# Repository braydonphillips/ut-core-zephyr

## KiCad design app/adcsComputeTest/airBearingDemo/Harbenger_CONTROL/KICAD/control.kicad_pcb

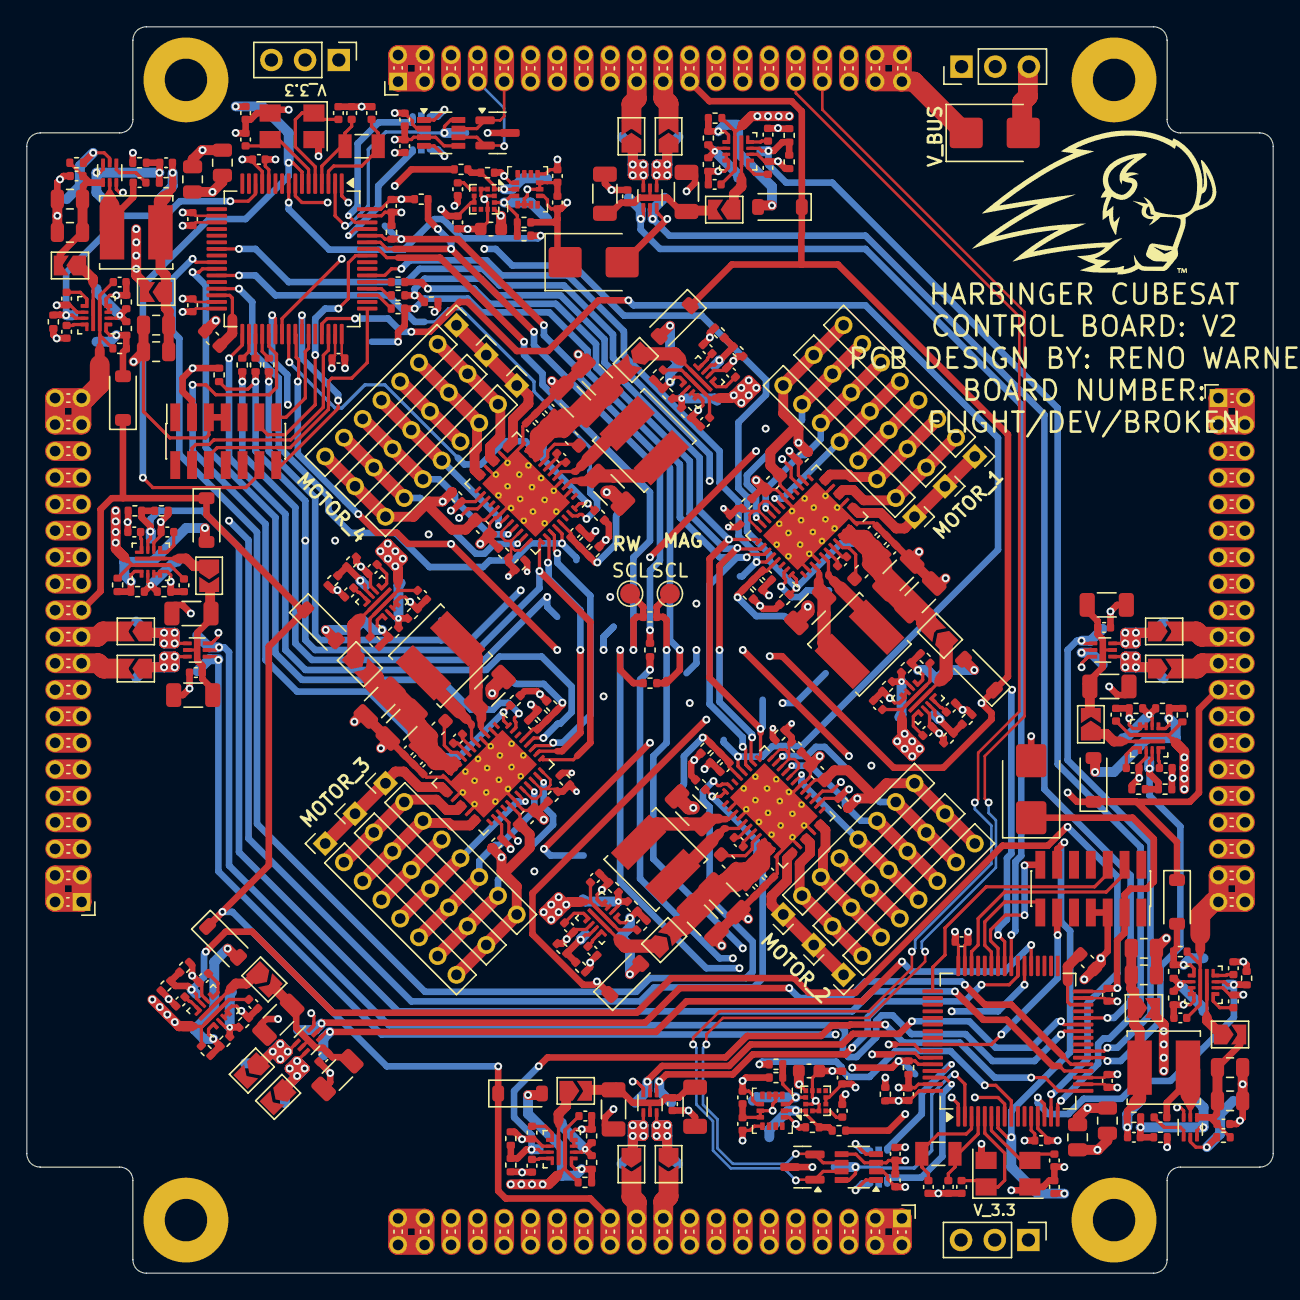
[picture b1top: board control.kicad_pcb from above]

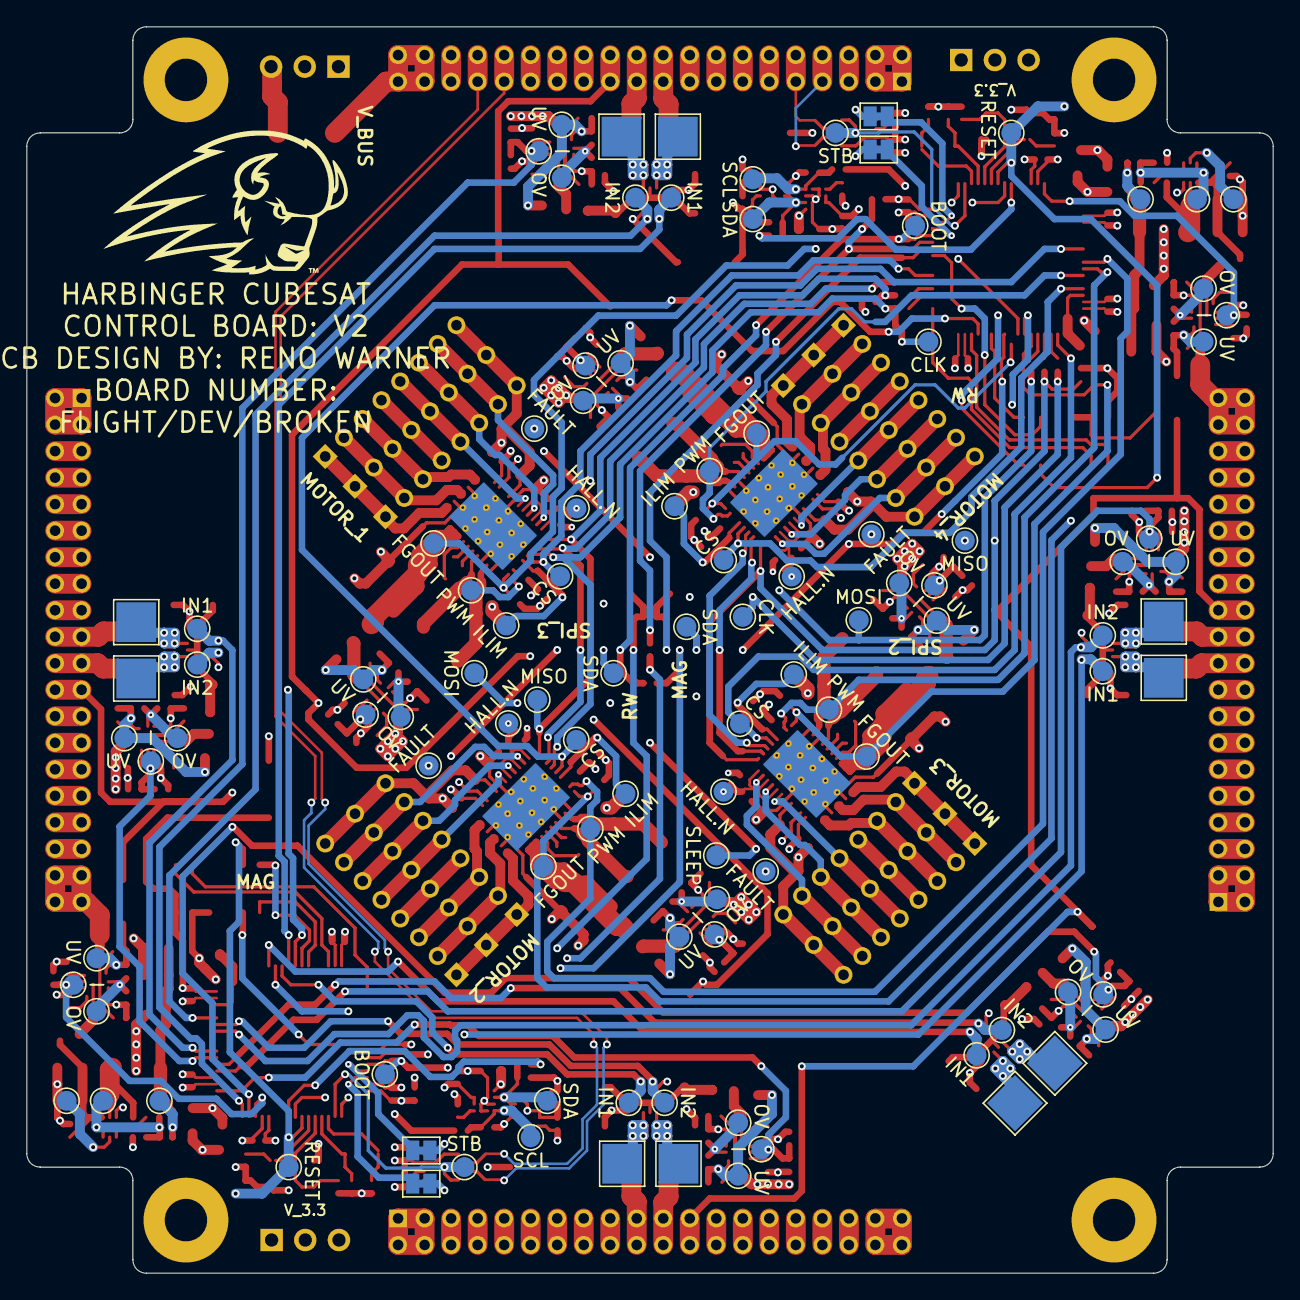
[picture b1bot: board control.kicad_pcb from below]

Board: 4 copper layers, 94.0 x 94.0 mm, 460 parts (106 on the bottom side), 301 nets.

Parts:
C1, C4, C5, C6, C8, C9, C10, C11, C12, C19, C22, C25, C27, C28, C31, C34, C37, C38, C39, C40, C41, C42, C49, C52, C53, C54, C55, C62, C65, C68, C69, C70, C71, C78, C81, C84, C87, C90, C93, C96, C98, C103, C104, C106, C108, C109, C110, C116, C117, C118, C121, C123, C128, C129, C131, C133, C134, C135, C141, C142: 100nF; C_0402_1005Metric
C2, C3, C23, C24, C32, C33, C35, C36, C50, C51, C63, C64, C79, C80, C85, C86, C88, C89, C94, C95, C119, C120: 4.7nF; C_0402_1005Metric
C7, C16, C18, C26, C46, C48, C59, C61, C75, C77: 1uF; C_0603_1608Metric
C13, C14, C15, C20, C21, C29, C30, C43, C44, C45, C56, C57, C58, C66, C67, C72, C73, C74, C82, C83, C91, C92: 22uF; C_1206_3216Metric
C17, C47, C60, C76: 47nF; C_0402_1005Metric
C97, C122: 47pF; C_0402_1005Metric
C99, C100, C101, C102, C105, C107, C124, C125, C126, C127, C130, C132: 10uF; C_0805_2012Metric
C111, C136: 4.7uF; C_0603_1608Metric
C112, C113, C137, C138: 6pF; C_0402_1005Metric
C114, C115, C139, C140: 12pF; C_0402_1005Metric
D1: SMBJ10A; D_SMB
D2, D6: SMLVT3V3; D_SMB
D3, D4, D5, D7, D8, D9, D10, D11, D12, D13, D14: BAT43W; D_SOD-123
D15, D16: ESD752DBZR; SOT-23
H1, H2, H3, H4: MountingHole_3.2mm_M3_Pad
J1, J2, J3, J4: TMM-120-01-F-D-RA; PinHeader_2x20_P2.00mm_Horizontal
J5, J6, J7, J8, J9, J10, J11, J12, J13, J14, J15, J16: CONN_1x08_2; PinHeader_1x08_P2.00mm_Vertical
J17, J18, J20: CONN_1x03_2.54; PinHeader_1x03_P2.54mm_Vertical
J19, J21: FTSH-107-01-L-DV-K; PinSocket_2x07_P1.27mm_Vertical_SMD
JP1, JP2, JP3, JP4, JP5, JP6, JP7, JP8, JP9, JP10, JP11, JP12, JP13, JP14, JP15, JP16, JP17, JP18, JP19, JP20, JP21, JP22, JP25: SolderJumper_2_Open; SolderJumper-2_P1.3mm_Open_TrianglePad1.0x1.5mm
JP23, JP24, JP26, JP27: Jumper_2_Bridged; SolderJumper-2_P1.3mm_Bridged_Pad1.0x1.5mm
L1, L2, L3, L4: LQH5BPN220MT0L; L_Murata_5x5
L5, L7: LQH5BPN2R2NT0L; L_Murata_5x5
R1, R5, R7, R8, R15, R16, R17, R18, R21, R22, R23, R24, R25, R28, R29, R31, R32, R33, R34, R36, R37, R38, R39, R40, R41, R42, R44, R45, R46, R47, R48, R49, R52, R53, R56, R57, R58, R59, R61, R62, R63, R64, R67, R68, R69, R70, R72, R73, R74, R75, R78, R79, R81, R82, R83, R84, R86, R87, R89, R90, R91, R92, R94, R95, R99, R101, R102, R106: 4.7kΩ; R_0402_1005Metric
R2, R3, R4, R9, R10, R11, R12, R13, R14, R19, R20, R50, R51: 100Ω; R_0402_1005Metric
R6, R30, R35, R43, R60, R71, R80, R85, R88, R93, R98, R100, R105: 30kΩ; R_0402_1005Metric
R26, R54, R65, R76: 220kΩ; R_0402_1005Metric
R27, R55, R66, R77, R96, R97, R103, R104: 133kΩ; R_0402_1005Metric
TP1, TP25, TP32, TP39, TP50, TP59, TP70, TP77, TP80, TP87, TP96: UV; TestPoint_Pad_D1.5mm
TP2, TP26, TP33, TP40, TP51, TP60, TP71, TP78, TP81, TP88, TP97: OV; TestPoint_Pad_D1.5mm
TP3, TP27, TP34, TP41, TP52, TP61, TP72, TP79, TP82, TP89, TP98: I; TestPoint_Pad_D1.5mm
TP4, TP7: MISO; TestPoint_Pad_D1.5mm
TP5, TP8: MOSI; TestPoint_Pad_D1.5mm
TP6, TP9: CLK; TestPoint_Pad_D1.5mm
TP10: SLEEP; TestPoint_Pad_D1.5mm
TP11, TP13, TP35, TP42: SCL; TestPoint_Pad_D1.5mm
TP12, TP14, TP36, TP43: SDA; TestPoint_Pad_D1.5mm
TP15, TP28, TP37, TP73, TP85: +; TestPoint_Pad_3.0x3.0mm
TP16, TP29, TP38, TP74, TP86: -; TestPoint_Pad_3.0x3.0mm
TP17, TP44, TP53, TP64: HALL.N; TestPoint_Pad_D1.5mm
TP18, TP45, TP54, TP65: ILIM; TestPoint_Pad_D1.5mm
TP19, TP46, TP55, TP66: FAULT; TestPoint_Pad_D1.5mm
TP20, TP47, TP56, TP67: FGOUT; TestPoint_Pad_D1.5mm
TP21, TP48, TP57, TP68: PWM; TestPoint_Pad_D1.5mm
TP22, TP49, TP58, TP69: CS; TestPoint_Pad_D1.5mm
TP23, TP30, TP62, TP75, TP83: IN1; TestPoint_Pad_D1.5mm
TP24, TP31, TP63, TP76, TP84: IN2; TestPoint_Pad_D1.5mm
TP90, TP99: EN; TestPoint_Pad_D1.5mm
TP91, TP100: V; TestPoint_Pad_D1.5mm
TP92, TP101: FB; TestPoint_Pad_D1.5mm
TP93, TP102: RESET; TestPoint_Pad_D1.5mm
TP94, TP103: BOOT; TestPoint_Pad_D1.5mm
TP95, TP104: STB; TestPoint_Pad_D1.5mm
U1, U6, U9, U10, U13, U15, U18, U20, U21, U23, U27: TPS259474L; Texas_RPW0010A
U2, U11: LSM6DSO; STM_LGA-14L
U3, U7: LIS3MDL; LGA-12_2x2mm_P0.5mm
U4, U12, U14, U17: MCT8316ZR; Texas_RGF40
U5, U8, U16, U19, U22: DRV8212DRL; Texas_DRL0006A
U24, U28: TPS562243; Texas_DRL0006A
U25, U29: STM32U5A5RJTx; LQFP-64_10x10mm_P0.5mm
U26, U30: TCAN3413DDFR; SOT-23-THIN
Y1, Y3: ECS-80-12-30BQ-JES-TR; Crystal_SMD_5032-4Pin_5.0x3.2mm
Y2, Y4: ECS-.327-6-34QCS-TR; Crystal_SMD_3215-2Pin_3.2x1.5mm

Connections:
/A.SCL: R3.2, TP13.1, U25.58 (PB6)
/A.SDA: R1.2, R2.2, TP14.1, U25.59 (PB7)
/B.SCL: R3.1, R5.2, TP35.1, U29.58 (PB6)
/B.SDA: R2.1, TP36.1, U29.59 (PB7)
/CAN_A.H: D15.1 (K), J2.9, J2.10, U26.7 (CAN_H)
/CAN_A.L: D15.2 (K), J2.7, J2.8, U26.6 (CAN_L)
/CAN_B.H: D16.1 (K), J2.31, J2.32, U30.7 (CAN_H)
/CAN_B.L: D16.2 (K), J2.33, J2.34, U30.6 (CAN_L)
/CONNECTOR_X+/GPIO: J2.29, J2.30
/CONNECTOR_X+/I2C.SCL: J2.15, J2.16
/CONNECTOR_X+/I2C.SDA: J2.13, J2.14
/CONNECTOR_X+/RESERVED: J2.17, J2.18
/CONNECTOR_X+/USB.DM: J2.27, J2.28
/CONNECTOR_X+/USB.DP: J2.25, J2.26
/CONNECTOR_X+/V_3.3: J2.11, J2.12
/CONNECTOR_X+/V_SOLAR: J2.1, J2.2, J2.3, J2.4
/CONNECTOR_X-/CAN_A.H: J1.9, J1.10
/CONNECTOR_X-/CAN_A.L: J1.7, J1.8
/CONNECTOR_X-/CAN_B.H: J1.31, J1.32
/CONNECTOR_X-/CAN_B.L: J1.33, J1.34
/CONNECTOR_X-/GPIO: J1.29, J1.30
/CONNECTOR_X-/I2C.SCL: J1.15, J1.16
/CONNECTOR_X-/I2C.SDA: J1.13, J1.14
/CONNECTOR_X-/RESERVED: J1.17, J1.18
/CONNECTOR_X-/USB.DM: J1.27, J1.28
/CONNECTOR_X-/USB.DP: J1.25, J1.26
/CONNECTOR_X-/V_3.3: J1.11, J1.12
/CONNECTOR_X-/V_SOLAR: J1.1, J1.2, J1.3, J1.4
/CONNECTOR_Y+/CAN_A.H: J3.9, J3.10
/CONNECTOR_Y+/CAN_A.L: J3.7, J3.8
/CONNECTOR_Y+/CAN_B.H: J3.31, J3.32
/CONNECTOR_Y+/CAN_B.L: J3.33, J3.34
/CONNECTOR_Y+/GPIO: J3.29, J3.30
/CONNECTOR_Y+/I2C.SCL: J3.15, J3.16
/CONNECTOR_Y+/I2C.SDA: J3.13, J3.14
/CONNECTOR_Y+/RESERVED: J3.17, J3.18
/CONNECTOR_Y+/USB.DM: J3.27, J3.28
/CONNECTOR_Y+/USB.DP: J3.25, J3.26
/CONNECTOR_Y+/V_3.3: J3.11, J3.12
/CONNECTOR_Y+/V_SOLAR: J3.1, J3.2, J3.3, J3.4
/CONNECTOR_Y-/CAN_A.H: J4.9, J4.10
/CONNECTOR_Y-/CAN_A.L: J4.7, J4.8
/CONNECTOR_Y-/CAN_B.H: J4.31, J4.32
/CONNECTOR_Y-/CAN_B.L: J4.33, J4.34
/CONNECTOR_Y-/GPIO: J4.29, J4.30
/CONNECTOR_Y-/I2C.SCL: J4.15, J4.16
/CONNECTOR_Y-/I2C.SDA: J4.13, J4.14
/CONNECTOR_Y-/RESERVED: J4.17, J4.18
/CONNECTOR_Y-/USB.DM: J4.27, J4.28
/CONNECTOR_Y-/USB.DP: J4.25, J4.26
/CONNECTOR_Y-/V_3.3: J4.11, J4.12
/CONNECTOR_Y-/V_SOLAR: J4.1, J4.2, J4.3, J4.4
/MAGNETORQUERS/COMMAND/EFUSE_LATCHED/DVDT: C120.1, U27.7 (DVDT)
/MAGNETORQUERS/COMMAND/EFUSE_LATCHED/ITIMER: C119.1, U27.10 (ITIMER)
/MAGNETORQUERS/COMMAND/EFUSE_LATCHED/OVLO: R101.2, R102.1, TP97.1, U27.2 (OVLO)
/MAGNETORQUERS/COMMAND/EFUSE_LATCHED/UVLO: D7.2 (A), R100.2, R101.1, TP96.1, U27.1 (EN/UVLO)
/MAGNETORQUERS/COMMAND/EFUSE_LATCHED/V_OUT: JP8.1 (A), U27.6 (OUT)
/MAGNETORQUERS/COMMAND/MCU/VCAP: C136.1, U29.30 (VCAP)
/MAGNETORQUERS/COMMAND/SMPS(3.3V)/SMPS/FB: C122.1, R103.2, R105.1, TP101.1, U28.6 (FB)
/MAGNETORQUERS/COMMAND/SMPS(3.3V)/SMPS/SW: C121.2, L7.1, U28.2 (SW)
/MAGNETORQUERS/COMMAND/SMPS(3.3V)/SMPS/V_OUT: C122.2, C126.1, C127.1, JP25.1 (A), L7.2, R103.1, TP100.1
/MAGNETORQUERS/COMMAND/SMPS(3.3V)/V_IN: C123.1, C124.1, C125.1, JP8.2 (B), R104.1, U28.1 (VIN)
/MAGNETORQUERS/COMMAND/SWD.NRST: C129.1, J21.12, TP102.1, U29.7 (NRST)
/MAGNETORQUERS/I2C_3.SCL: R48.1, R50.2, TP42.1, U2.13 (SCL/SPC), U3.1 (SCL/SPL)
/MAGNETORQUERS/I2C_3.SDA: R49.1, R51.2, TP43.1, U2.14 (SDA/SDI/SDO), U3.11 (SDA/SDI/SDO)
/MAGNETORQUERS/MAGNETORQUER_X+/BRUSHED_DRIVER/OUT_1: JP20.1 (A), TP85.1, U22.6 (OUT1)
/MAGNETORQUERS/MAGNETORQUER_X+/BRUSHED_DRIVER/OUT_2: JP21.1 (A), TP86.1, U22.4 (OUT2)
/MAGNETORQUERS/MAGNETORQUER_X+/BRUSHED_DRIVER/V_IN: C90.1, C91.1, C92.1, JP19.2 (B), U22.5 (VM)
/MAGNETORQUERS/MAGNETORQUER_X+/EFUSE_LATCHED/DVDT: C89.1, U21.7 (DVDT)
/MAGNETORQUERS/MAGNETORQUER_X+/EFUSE_LATCHED/ITIMER: C88.1, U21.10 (ITIMER)
/MAGNETORQUERS/MAGNETORQUER_X+/EFUSE_LATCHED/OVLO: R89.2, R90.1, TP81.1, U21.2 (OVLO)
/MAGNETORQUERS/MAGNETORQUER_X+/EFUSE_LATCHED/UVLO: D14.2 (A), R88.2, R89.1, TP80.1, U21.1 (EN/UVLO)
/MAGNETORQUERS/MAGNETORQUER_X+/EFUSE_LATCHED/V_OUT: JP19.1 (A), U21.6 (OUT)
/MAGNETORQUERS/MAGNETORQUER_X-/BRUSHED_DRIVER/OUT_1: JP3.1 (A), TP15.1, U5.6 (OUT1)
/MAGNETORQUERS/MAGNETORQUER_X-/BRUSHED_DRIVER/OUT_2: JP4.1 (A), TP16.1, U5.4 (OUT2)
/MAGNETORQUERS/MAGNETORQUER_X-/BRUSHED_DRIVER/V_IN: C19.1, C20.1, C21.1, JP2.2 (B), U5.5 (VM)
/MAGNETORQUERS/MAGNETORQUER_X-/EFUSE_LATCHED/DVDT: C24.1, U6.7 (DVDT)
/MAGNETORQUERS/MAGNETORQUER_X-/EFUSE_LATCHED/ITIMER: C23.1, U6.10 (ITIMER)
/MAGNETORQUERS/MAGNETORQUER_X-/EFUSE_LATCHED/OVLO: R31.2, R32.1, TP26.1, U6.2 (OVLO)
/MAGNETORQUERS/MAGNETORQUER_X-/EFUSE_LATCHED/UVLO: D4.2 (A), R30.2, R31.1, TP25.1, U6.1 (EN/UVLO)
/MAGNETORQUERS/MAGNETORQUER_X-/EFUSE_LATCHED/V_OUT: JP2.1 (A), U6.6 (OUT)
/MAGNETORQUERS/MAGNETORQUER_Y+/BRUSHED_DRIVER/OUT_1: JP6.1 (A), TP28.1, U8.6 (OUT1)
/MAGNETORQUERS/MAGNETORQUER_Y+/BRUSHED_DRIVER/OUT_2: JP7.1 (A), TP29.1, U8.4 (OUT2)
/MAGNETORQUERS/MAGNETORQUER_Y+/BRUSHED_DRIVER/V_IN: C28.1, C29.1, C30.1, JP5.2 (B), U8.5 (VM)
/MAGNETORQUERS/MAGNETORQUER_Y+/EFUSE_LATCHED/DVDT: C33.1, U9.7 (DVDT)
/MAGNETORQUERS/MAGNETORQUER_Y+/EFUSE_LATCHED/ITIMER: C32.1, U9.10 (ITIMER)
/MAGNETORQUERS/MAGNETORQUER_Y+/EFUSE_LATCHED/OVLO: R36.2, R37.1, TP33.1, U9.2 (OVLO)
/MAGNETORQUERS/MAGNETORQUER_Y+/EFUSE_LATCHED/UVLO: D5.2 (A), R35.2, R36.1, TP32.1, U9.1 (EN/UVLO)
/MAGNETORQUERS/MAGNETORQUER_Y+/EFUSE_LATCHED/V_OUT: JP5.1 (A), U9.6 (OUT)
/MAGNETORQUERS/MAGNETORQUER_Y-/BRUSHED_DRIVER/OUT_1: JP10.1 (A), TP37.1, U16.6 (OUT1)
/MAGNETORQUERS/MAGNETORQUER_Y-/BRUSHED_DRIVER/OUT_2: JP11.1 (A), TP38.1, U16.4 (OUT2)
/MAGNETORQUERS/MAGNETORQUER_Y-/BRUSHED_DRIVER/V_IN: C65.1, C66.1, C67.1, JP9.2 (B), U16.5 (VM)
/MAGNETORQUERS/MAGNETORQUER_Y-/EFUSE_LATCHED/DVDT: C80.1, U18.7 (DVDT)
/MAGNETORQUERS/MAGNETORQUER_Y-/EFUSE_LATCHED/ITIMER: C79.1, U18.10 (ITIMER)
/MAGNETORQUERS/MAGNETORQUER_Y-/EFUSE_LATCHED/OVLO: R81.2, R82.1, TP71.1, U18.2 (OVLO)
/MAGNETORQUERS/MAGNETORQUER_Y-/EFUSE_LATCHED/UVLO: D8.2 (A), R80.2, R81.1, TP70.1, U18.1 (EN/UVLO)
/MAGNETORQUERS/MAGNETORQUER_Y-/EFUSE_LATCHED/V_OUT: JP9.1 (A), U18.6 (OUT)
/MAGNETORQUERS/MAGNETORQUER_Z/BRUSHED_DRIVER/OUT_1: JP17.1 (A), TP73.1, U19.6 (OUT1)
/MAGNETORQUERS/MAGNETORQUER_Z/BRUSHED_DRIVER/OUT_2: JP18.1 (A), TP74.1, U19.4 (OUT2)
/MAGNETORQUERS/MAGNETORQUER_Z/BRUSHED_DRIVER/V_IN: C81.1, C82.1, C83.1, JP16.2 (B), U19.5 (VM)
/MAGNETORQUERS/MAGNETORQUER_Z/EFUSE_LATCHED/DVDT: C86.1, U20.7 (DVDT)
/MAGNETORQUERS/MAGNETORQUER_Z/EFUSE_LATCHED/ITIMER: C85.1, U20.10 (ITIMER)
/MAGNETORQUERS/MAGNETORQUER_Z/EFUSE_LATCHED/OVLO: R86.2, R87.1, TP78.1, U20.2 (OVLO)
/MAGNETORQUERS/MAGNETORQUER_Z/EFUSE_LATCHED/UVLO: D13.2 (A), R85.2, R86.1, TP77.1, U20.1 (EN/UVLO)
/MAGNETORQUERS/MAGNETORQUER_Z/EFUSE_LATCHED/V_OUT: JP16.1 (A), U20.6 (OUT)
/MAGNETORQUERS/PA0: R38.2, TP98.1, U27.9 (ILM), U29.14 (PA0)
/MAGNETORQUERS/PA1: R83.2, R84.2, TP79.1, U20.9 (ILM), U29.15 (PA1)
/MAGNETORQUERS/PA2: R91.2, R92.2, TP82.1, U21.9 (ILM), U29.16 (PA2)
/MAGNETORQUERS/PA3: R22.2, R23.2, TP27.1, U6.9 (ILM), U29.17 (PA3)
/MAGNETORQUERS/PA4: R33.2, R34.2, TP34.1, U9.9 (ILM), U29.20 (PA4)
/MAGNETORQUERS/PA5: TP76.1, U19.2 (IN2), U29.21 (PA5)
/MAGNETORQUERS/PA6: R39.2, R40.2, TP72.1, U18.9 (ILM), U29.22 (PA6)
/MAGNETORQUERS/PA7: TP62.1, U16.1 (IN1), U29.23 (PA7)
/MAGNETORQUERS/PA8: TP63.1, U16.2 (IN2), U29.41 (PA8)
/MAGNETORQUERS/PA9: J21.14, U29.42 (PA9)
/MAGNETORQUERS/PA10: J21.13, U29.43 (PA10)
/MAGNETORQUERS/PA13: J21.4, U29.46 (PA13)
/MAGNETORQUERS/PA14: J21.6, U29.49 (PA14)
/MAGNETORQUERS/PB0: TP31.1, U8.2 (IN2), U29.26 (PB0)
/MAGNETORQUERS/PB1: TP24.1, U5.2 (IN2), U29.27 (PB1)
/MAGNETORQUERS/PB2: TP84.1, U22.2 (IN2), U29.28 (PB2)
/MAGNETORQUERS/PB5: J21.11, U29.57 (PB5)
/MAGNETORQUERS/PB8: JP27.1 (A), U29.61 (PB8)
/MAGNETORQUERS/PB9: JP26.1 (A), U29.62 (PB9)
/MAGNETORQUERS/PC0: R50.1, U29.8 (PC0)
/MAGNETORQUERS/PC1: R51.1, U29.9 (PC1)
/MAGNETORQUERS/PC6: TP75.1, U19.1 (IN1), U29.37 (PC6)
/MAGNETORQUERS/PC7: TP30.1, U8.1 (IN1), U29.38 (PC7)
/MAGNETORQUERS/PC8: TP23.1, U5.1 (IN1), U29.39 (PC8)
/MAGNETORQUERS/PC9: TP83.1, U22.1 (IN1), U29.40 (PC9)
/MAGNETORQUERS/PC13: TP104.1, U29.2 (PC13), U30.8 (STB)
/MAGNETORQUERS/PC14: C138.1, U29.3 (PC14), Y4.2
/MAGNETORQUERS/PC15: C137.1, U29.4 (PC15), Y4.1
/MAGNETORQUERS/PH0: C139.1, U29.5 (PH0), Y3.1
/MAGNETORQUERS/PH1: C140.2, U29.6 (PH1), Y3.3
/MAGNETORQUERS/PH3: R4.1, R106.1, TP103.1, U29.60 (PH3)
/MAGNETORQUERS/V_3.3: C4.1, C5.1, C6.1, C7.1, C128.1, C130.1, C131.1, C132.1, C133.1, C134.1, C135.1, C141.1, C142.1, D6.1 (K), J20.2, J21.3, JP25.2 (B), R5.1, R48.2, R49.2, U2.5 (VDD_IO), U2.8 (VDD), U2.12 (CS), U3.5 (VDD), U3.6 (VDD_IO), U3.10 (CS), U29.1 (VBAT), U29.13 (VDDA), U29.19 (VDD), U29.32 (VDD), U29.48 (VDDUSB), U29.64 (VDD), U30.3 (VCC), U30.5 (V_IO)
/MAGNET_X+.+: J2.19, J2.20, JP20.2 (B)
/MAGNET_X+.-: J2.21, J2.22, JP21.2 (B)
/MAGNET_X-.+: J1.19, J1.20, JP3.2 (B)
/MAGNET_X-.-: J1.21, J1.22, JP4.2 (B)
/MAGNET_Y+.+: J3.19, J3.20, JP6.2 (B)
/MAGNET_Y+.-: J3.21, J3.22, JP7.2 (B)
/MAGNET_Y-.+: J4.19, J4.20, JP10.2 (B)
/MAGNET_Y-.-: J4.21, J4.22, JP11.2 (B)
/REACTION WHEELS/COMMAND/EFUSE_LATCHED/DVDT: C95.1, U23.7 (DVDT)
/REACTION WHEELS/COMMAND/EFUSE_LATCHED/ITIMER: C94.1, U23.10 (ITIMER)
/REACTION WHEELS/COMMAND/EFUSE_LATCHED/OVLO: R94.2, R95.1, TP88.1, U23.2 (OVLO)
/REACTION WHEELS/COMMAND/EFUSE_LATCHED/UVLO: D3.2 (A), R93.2, R94.1, TP87.1, U23.1 (EN/UVLO)
/REACTION WHEELS/COMMAND/EFUSE_LATCHED/V_OUT: JP1.1 (A), U23.6 (OUT)
/REACTION WHEELS/COMMAND/MCU/VCAP: C111.1, U25.30 (VCAP)
/REACTION WHEELS/COMMAND/SMPS(3.3V)/SMPS/FB: C97.1, R96.2, R98.1, TP92.1, U24.6 (FB)
/REACTION WHEELS/COMMAND/SMPS(3.3V)/SMPS/SW: C96.2, L5.1, U24.2 (SW)
/REACTION WHEELS/COMMAND/SMPS(3.3V)/SMPS/V_OUT: C97.2, C101.1, C102.1, JP22.1 (A), L5.2, R96.1, TP91.1
/REACTION WHEELS/COMMAND/SMPS(3.3V)/V_IN: C98.1, C99.1, C100.1, JP1.2 (B), R97.1, U24.1 (VIN)
/REACTION WHEELS/COMMAND/SWD.NRST: C104.1, J19.12, TP93.1, U25.7 (NRST)
/REACTION WHEELS/CONTROL_1.CS: TP22.1, U4.36 (nSCS), U25.54 (PD2)
/REACTION WHEELS/CONTROL_1.FAULT: R29.2, TP19.1, U4.22 (nFAULT)
/REACTION WHEELS/CONTROL_1.FGOUT: R28.2, TP20.1, U4.40 (FGOUT), U25.39 (PC8)
/REACTION WHEELS/CONTROL_1.PWM: TP21.1, U4.39 (PWM), U25.23 (PA7)
/REACTION WHEELS/CONTROL_2.CS: TP49.1, U12.36 (nSCS), U25.45 (PA12)
/REACTION WHEELS/CONTROL_2.FAULT: R57.2, TP46.1, U12.22 (nFAULT)
/REACTION WHEELS/CONTROL_2.FGOUT: R56.2, TP47.1, U12.40 (FGOUT), U25.38 (PC7)
/REACTION WHEELS/CONTROL_2.PWM: TP48.1, U12.39 (PWM), U25.25 (PC5)
/REACTION WHEELS/CONTROL_3.CS: TP58.1, U14.36 (nSCS), U25.33 (PB12)
/REACTION WHEELS/CONTROL_3.FAULT: R68.2, TP55.1, U14.22 (nFAULT)
/REACTION WHEELS/CONTROL_3.FGOUT: R67.2, TP56.1, U14.40 (FGOUT), U25.37 (PC6)
/REACTION WHEELS/CONTROL_3.PWM: TP57.1, U14.39 (PWM), U25.26 (PB0)
/REACTION WHEELS/CONTROL_3.SLEEP: TP10.1, U4.23 (nSLEEP), U12.23 (nSLEEP), U14.23 (nSLEEP), U17.23 (nSLEEP), U25.41 (PA8)
/REACTION WHEELS/CONTROL_4.CS: TP69.1, U17.36 (nSCS), U25.29 (PB10)
/REACTION WHEELS/CONTROL_4.FAULT: R79.2, TP66.1, U17.22 (nFAULT)
/REACTION WHEELS/CONTROL_4.FGOUT: R78.2, TP67.1, U17.40 (FGOUT), U25.40 (PC9)
/REACTION WHEELS/CONTROL_4.PWM: TP68.1, U17.39 (PWM), U25.27 (PB1)
/REACTION WHEELS/I2C_3.SCL: R17.1, R19.2, TP11.1, U7.1 (SCL/SPL), U11.13 (SCL/SPC)
/REACTION WHEELS/I2C_3.SDA: R18.1, R20.2, TP12.1, U7.11 (SDA/SDI/SDO), U11.14 (SDA/SDI/SDO)
/REACTION WHEELS/PA0: R21.2, TP89.1, U23.9 (ILM), U25.14 (PA0)
/REACTION WHEELS/PA9: J19.14, U25.42 (PA9)
/REACTION WHEELS/PA10: J19.13, U25.43 (PA10)
/REACTION WHEELS/PA13: J19.4, U25.46 (PA13)
/REACTION WHEELS/PA14: J19.6, U25.49 (PA14)
/REACTION WHEELS/PB5: J19.11, U25.57 (PB5)
/REACTION WHEELS/PB8: JP24.1 (A), U25.61 (PB8)
/REACTION WHEELS/PB9: JP23.1 (A), U25.62 (PB9)
/REACTION WHEELS/PB13: R11.1, U25.34 (PB13)
/REACTION WHEELS/PB14: R9.1, U25.35 (PB14)
/REACTION WHEELS/PB15: R10.1, U25.36 (PB15)
/REACTION WHEELS/PC0: R19.1, U25.8 (PC0)
/REACTION WHEELS/PC1: R20.1, U25.9 (PC1)
/REACTION WHEELS/PC10: R14.1, U25.51 (PC10)
/REACTION WHEELS/PC11: R12.1, U25.52 (PC11)
/REACTION WHEELS/PC12: R13.1, U25.53 (PC12)
/REACTION WHEELS/PC13: TP95.1, U25.2 (PC13), U26.8 (STB)
/REACTION WHEELS/PC14: C113.1, U25.3 (PC14), Y2.2
/REACTION WHEELS/PC15: C112.1, U25.4 (PC15), Y2.1
/REACTION WHEELS/PH0: C114.1, U25.5 (PH0), Y1.1
/REACTION WHEELS/PH1: C115.2, U25.6 (PH1), Y1.3
/REACTION WHEELS/PH3: R4.2, R99.1, TP94.1, U25.60 (PH3)
/REACTION WHEELS/REACTION_WHEEL_1/BLDC_MOTOR_DRIVER/HALL.A: J8.5, J9.5, J10.5, U4.27 (HPA)
/REACTION WHEELS/REACTION_WHEEL_1/BLDC_MOTOR_DRIVER/HALL.B: J8.7, J9.7, J10.7, U4.31 (HPC)
/REACTION WHEELS/REACTION_WHEEL_1/BLDC_MOTOR_DRIVER/HALL.C: J8.6, J9.6, J10.6, U4.29 (HPB)
/REACTION WHEELS/REACTION_WHEEL_1/BLDC_MOTOR_DRIVER/HALL.N: R24.2, R25.1, TP17.1, U4.28 (HNA), U4.30 (HNB), U4.32 (HNC)
/REACTION WHEELS/REACTION_WHEEL_1/BLDC_MOTOR_DRIVER/ILIM: C10.1, R26.2, R27.1, TP18.1, U4.37 (ILIM)
/REACTION WHEELS/REACTION_WHEEL_1/BLDC_MOTOR_DRIVER/MOTOR.A: J8.1, J9.1, J10.1, U4.13 (OUTA), U4.14 (OUTA)
/REACTION WHEELS/REACTION_WHEEL_1/BLDC_MOTOR_DRIVER/MOTOR.B: J8.2, J9.2, J10.2, U4.16 (OUTB), U4.17 (OUTB)
/REACTION WHEELS/REACTION_WHEEL_1/BLDC_MOTOR_DRIVER/MOTOR.C: J8.3, J9.3, J10.3, U4.19 (OUTC), U4.20 (OUTC)
/REACTION WHEELS/REACTION_WHEEL_1/BLDC_MOTOR_DRIVER/V_AVDD: C18.1, J8.8, J9.8, J10.8, R24.1, R26.1, R28.1, R29.1, U4.25 (AVDD)
/REACTION WHEELS/REACTION_WHEEL_1/BLDC_MOTOR_DRIVER/V_IN: C9.2, C11.2, C12.2, C13.1, C14.1, C16.1, JP13.2 (B), U4.9 (VM), U4.10 (VM), U4.11 (VM)
/REACTION WHEELS/REACTION_WHEEL_1/EFUSE_LATCHED/DVDT: C3.1, U1.7 (DVDT)
/REACTION WHEELS/REACTION_WHEEL_1/EFUSE_LATCHED/ITIMER: C2.1, U1.10 (ITIMER)
/REACTION WHEELS/REACTION_WHEEL_1/EFUSE_LATCHED/I_LIM: R46.2, R47.2, TP3.1, U1.9 (ILM)
/REACTION WHEELS/REACTION_WHEEL_1/EFUSE_LATCHED/OVLO: R7.2, R8.1, TP2.1, U1.2 (OVLO)
/REACTION WHEELS/REACTION_WHEEL_1/EFUSE_LATCHED/UVLO: D10.2 (A), R6.2, R7.1, TP1.1, U1.1 (EN/UVLO)
/REACTION WHEELS/REACTION_WHEEL_1/EFUSE_LATCHED/V_OUT: JP13.1 (A), U1.6 (OUT)
/REACTION WHEELS/REACTION_WHEEL_2/BLDC_MOTOR_DRIVER/HALL.A: J5.5, J6.5, J7.5, U12.27 (HPA)
/REACTION WHEELS/REACTION_WHEEL_2/BLDC_MOTOR_DRIVER/HALL.B: J5.7, J6.7, J7.7, U12.31 (HPC)
/REACTION WHEELS/REACTION_WHEEL_2/BLDC_MOTOR_DRIVER/HALL.C: J5.6, J6.6, J7.6, U12.29 (HPB)
/REACTION WHEELS/REACTION_WHEEL_2/BLDC_MOTOR_DRIVER/HALL.N: R52.2, R53.1, TP44.1, U12.28 (HNA), U12.30 (HNB), U12.32 (HNC)
/REACTION WHEELS/REACTION_WHEEL_2/BLDC_MOTOR_DRIVER/ILIM: C40.1, R54.2, R55.1, TP45.1, U12.37 (ILIM)
/REACTION WHEELS/REACTION_WHEEL_2/BLDC_MOTOR_DRIVER/MOTOR.A: J5.1, J6.1, J7.1, U12.13 (OUTA), U12.14 (OUTA)
/REACTION WHEELS/REACTION_WHEEL_2/BLDC_MOTOR_DRIVER/MOTOR.B: J5.2, J6.2, J7.2, U12.16 (OUTB), U12.17 (OUTB)
/REACTION WHEELS/REACTION_WHEEL_2/BLDC_MOTOR_DRIVER/MOTOR.C: J5.3, J6.3, J7.3, U12.19 (OUTC), U12.20 (OUTC)
/REACTION WHEELS/REACTION_WHEEL_2/BLDC_MOTOR_DRIVER/V_AVDD: C48.1, J5.8, J6.8, J7.8, R52.1, R54.1, R56.1, R57.1, U12.25 (AVDD)
/REACTION WHEELS/REACTION_WHEEL_2/BLDC_MOTOR_DRIVER/V_IN: C39.2, C41.2, C42.2, C43.1, C44.1, C46.1, JP12.2 (B), U12.9 (VM), U12.10 (VM), U12.11 (VM)
/REACTION WHEELS/REACTION_WHEEL_2/EFUSE_LATCHED/DVDT: C36.1, U10.7 (DVDT)
/REACTION WHEELS/REACTION_WHEEL_2/EFUSE_LATCHED/ITIMER: C35.1, U10.10 (ITIMER)
/REACTION WHEELS/REACTION_WHEEL_2/EFUSE_LATCHED/I_LIM: R41.2, R42.2, TP41.1, U10.9 (ILM)
/REACTION WHEELS/REACTION_WHEEL_2/EFUSE_LATCHED/OVLO: R44.2, R45.1, TP40.1, U10.2 (OVLO)
/REACTION WHEELS/REACTION_WHEEL_2/EFUSE_LATCHED/UVLO: D9.2 (A), R43.2, R44.1, TP39.1, U10.1 (EN/UVLO)
/REACTION WHEELS/REACTION_WHEEL_2/EFUSE_LATCHED/V_OUT: JP12.1 (A), U10.6 (OUT)
/REACTION WHEELS/REACTION_WHEEL_3/BLDC_MOTOR_DRIVER/HALL.A: J11.5, J12.5, J13.5, U14.27 (HPA)
/REACTION WHEELS/REACTION_WHEEL_3/BLDC_MOTOR_DRIVER/HALL.B: J11.7, J12.7, J13.7, U14.31 (HPC)
/REACTION WHEELS/REACTION_WHEEL_3/BLDC_MOTOR_DRIVER/HALL.C: J11.6, J12.6, J13.6, U14.29 (HPB)
/REACTION WHEELS/REACTION_WHEEL_3/BLDC_MOTOR_DRIVER/HALL.N: R63.2, R64.1, TP53.1, U14.28 (HNA), U14.30 (HNB), U14.32 (HNC)
/REACTION WHEELS/REACTION_WHEEL_3/BLDC_MOTOR_DRIVER/ILIM: C53.1, R65.2, R66.1, TP54.1, U14.37 (ILIM)
/REACTION WHEELS/REACTION_WHEEL_3/BLDC_MOTOR_DRIVER/MOTOR.A: J11.1, J12.1, J13.1, U14.13 (OUTA), U14.14 (OUTA)
/REACTION WHEELS/REACTION_WHEEL_3/BLDC_MOTOR_DRIVER/MOTOR.B: J11.2, J12.2, J13.2, U14.16 (OUTB), U14.17 (OUTB)
/REACTION WHEELS/REACTION_WHEEL_3/BLDC_MOTOR_DRIVER/MOTOR.C: J11.3, J12.3, J13.3, U14.19 (OUTC), U14.20 (OUTC)
/REACTION WHEELS/REACTION_WHEEL_3/BLDC_MOTOR_DRIVER/V_AVDD: C61.1, J11.8, J12.8, J13.8, R63.1, R65.1, R67.1, R68.1, U14.25 (AVDD)
/REACTION WHEELS/REACTION_WHEEL_3/BLDC_MOTOR_DRIVER/V_IN: C52.2, C54.2, C55.2, C56.1, C57.1, C59.1, JP14.2 (B), U14.9 (VM), U14.10 (VM), U14.11 (VM)
/REACTION WHEELS/REACTION_WHEEL_3/EFUSE_LATCHED/DVDT: C51.1, U13.7 (DVDT)
/REACTION WHEELS/REACTION_WHEEL_3/EFUSE_LATCHED/ITIMER: C50.1, U13.10 (ITIMER)
/REACTION WHEELS/REACTION_WHEEL_3/EFUSE_LATCHED/I_LIM: R58.2, R59.2, TP52.1, U13.9 (ILM)
/REACTION WHEELS/REACTION_WHEEL_3/EFUSE_LATCHED/OVLO: R61.2, R62.1, TP51.1, U13.2 (OVLO)
/REACTION WHEELS/REACTION_WHEEL_3/EFUSE_LATCHED/UVLO: D11.2 (A), R60.2, R61.1, TP50.1, U13.1 (EN/UVLO)
/REACTION WHEELS/REACTION_WHEEL_3/EFUSE_LATCHED/V_OUT: JP14.1 (A), U13.6 (OUT)
/REACTION WHEELS/REACTION_WHEEL_4/BLDC_MOTOR_DRIVER/HALL.A: J14.5, J15.5, J16.5, U17.27 (HPA)
/REACTION WHEELS/REACTION_WHEEL_4/BLDC_MOTOR_DRIVER/HALL.B: J14.7, J15.7, J16.7, U17.31 (HPC)
/REACTION WHEELS/REACTION_WHEEL_4/BLDC_MOTOR_DRIVER/HALL.C: J14.6, J15.6, J16.6, U17.29 (HPB)
/REACTION WHEELS/REACTION_WHEEL_4/BLDC_MOTOR_DRIVER/HALL.N: R74.2, R75.1, TP64.1, U17.28 (HNA), U17.30 (HNB), U17.32 (HNC)
/REACTION WHEELS/REACTION_WHEEL_4/BLDC_MOTOR_DRIVER/ILIM: C69.1, R76.2, R77.1, TP65.1, U17.37 (ILIM)
/REACTION WHEELS/REACTION_WHEEL_4/BLDC_MOTOR_DRIVER/MOTOR.A: J14.1, J15.1, J16.1, U17.13 (OUTA), U17.14 (OUTA)
/REACTION WHEELS/REACTION_WHEEL_4/BLDC_MOTOR_DRIVER/MOTOR.B: J14.2, J15.2, J16.2, U17.16 (OUTB), U17.17 (OUTB)
/REACTION WHEELS/REACTION_WHEEL_4/BLDC_MOTOR_DRIVER/MOTOR.C: J14.3, J15.3, J16.3, U17.19 (OUTC), U17.20 (OUTC)
/REACTION WHEELS/REACTION_WHEEL_4/BLDC_MOTOR_DRIVER/V_AVDD: C77.1, J14.8, J15.8, J16.8, R74.1, R76.1, R78.1, R79.1, U17.25 (AVDD)
/REACTION WHEELS/REACTION_WHEEL_4/BLDC_MOTOR_DRIVER/V_IN: C68.2, C70.2, C71.2, C72.1, C73.1, C75.1, JP15.2 (B), U17.9 (VM), U17.10 (VM), U17.11 (VM)
/REACTION WHEELS/REACTION_WHEEL_4/EFUSE_LATCHED/DVDT: C64.1, U15.7 (DVDT)
/REACTION WHEELS/REACTION_WHEEL_4/EFUSE_LATCHED/ITIMER: C63.1, U15.10 (ITIMER)
/REACTION WHEELS/REACTION_WHEEL_4/EFUSE_LATCHED/I_LIM: R69.2, R70.2, TP61.1, U15.9 (ILM)
/REACTION WHEELS/REACTION_WHEEL_4/EFUSE_LATCHED/OVLO: R72.2, R73.1, TP60.1, U15.2 (OVLO)
/REACTION WHEELS/REACTION_WHEEL_4/EFUSE_LATCHED/UVLO: D12.2 (A), R71.2, R72.1, TP59.1, U15.1 (EN/UVLO)
/REACTION WHEELS/REACTION_WHEEL_4/EFUSE_LATCHED/V_OUT: JP15.1 (A), U15.6 (OUT)
/REACTION WHEELS/SPI_2.CLK: R11.2, TP6.1, U14.35 (SCLK), U17.35 (SCLK)
/REACTION WHEELS/SPI_2.MISO: R9.2, R15.2, TP4.1, U14.33 (SDO), U17.33 (SDO)
/REACTION WHEELS/SPI_2.MOSI: R10.2, TP5.1, U14.34 (SDI), U17.34 (SDI)
/REACTION WHEELS/SPI_3.CLK: R14.2, TP9.1, U4.35 (SCLK), U12.35 (SCLK)
/REACTION WHEELS/SPI_3.MISO: R12.2, R16.2, TP7.1, U4.33 (SDO), U12.33 (SDO)
/REACTION WHEELS/SPI_3.MOSI: R13.2, TP8.1, U4.34 (SDI), U12.34 (SDI)
/REACTION WHEELS/V_3.3: C25.1, C26.1, C37.1, C38.1, C103.1, C105.1, C106.1, C107.1, C108.1, C109.1, C110.1, C116.1, C117.1, D2.1 (K), J18.2, J19.3, JP22.2 (B), R1.1, R15.1, R16.1, R17.2, R18.2, U7.5 (VDD), U7.6 (VDD_IO), U7.10 (CS), U11.5 (VDD_IO), U11.8 (VDD), U11.12 (CS), U25.1 (VBAT), U25.13 (VDDA), U25.19 (VDD), U25.32 (VDD), U25.48 (VDDUSB), U25.64 (VDD), U26.3 (VCC), U26.5 (V_IO)
/SHUTDOWN: D3.1 (K), D4.1 (K), D5.1 (K), D7.1 (K), D8.1 (K), D9.1 (K), D10.1 (K), D11.1 (K), D12.1 (K), D13.1 (K), D14.1 (K), J1.23, J1.24, J2.23, J2.24, J3.23, J3.24, J4.23, J4.24
/V_BUS: C1.1, C22.1, C31.1, C34.1, C49.1, C62.1, C78.1, C84.1, C87.1, C93.1, C118.1, D1.1 (K), J1.37, J1.38, J1.39, J1.40, J2.37, J2.38, J2.39, J2.40, J3.37, J3.38, J3.39, J3.40, J4.37, J4.38, J4.39, J4.40, J17.2, R6.1, R30.1, R35.1, R43.1, R60.1, R71.1, R80.1, R85.1, R88.1, R93.1, R100.1, U1.5 (IN), U6.5 (IN), U9.5 (IN), U10.5 (IN), U13.5 (IN), U15.5 (IN), U18.5 (IN), U20.5 (IN), U21.5 (IN), U23.5 (IN), U27.5 (IN)
/V_GND: C1.2, C2.2, C3.2, C4.2, C5.2, C6.2, C7.2, C8.2, C9.1, C10.2, C11.1, C12.1, C13.2, C14.2, C15.1, C18.2, C19.2, C20.2, C21.2, C22.2, C23.2, C24.2, C25.2, C26.2, C27.2, C28.2, C29.2, C30.2, C31.2, C32.2, C33.2, C34.2, C35.2, C36.2, C37.2, C38.2, C39.1, C40.2, C41.1, C42.1, C43.2, C44.2, C45.1, C48.2, C49.2, C50.2, C51.2, C52.1, C53.2, C54.1, C55.1, C56.2, C57.2, C58.1, C61.2, C62.2, C63.2, C64.2, C65.2, C66.2, C67.2, C68.1, C69.2, C70.1, C71.1, C72.2, C73.2, C74.1, C77.2, C78.2, C79.2, C80.2, C81.2, C82.2, C83.2, C84.2, C85.2, C86.2, C87.2, C88.2, C89.2, C90.2, C91.2, C92.2, C93.2, C94.2, C95.2, C98.2, C99.2, C100.2, C101.2, C102.2, C103.2, C104.2, C105.2, C106.2, C107.2, C108.2, C109.2, C110.2, C111.2, C112.2, C113.2, C114.2, C115.1, C116.2, C117.2, C118.2, C119.2, C120.2, C123.2, C124.2, C125.2, C126.2, C127.2, C128.2, C129.2, C130.2, C131.2, C132.2, C133.2, C134.2, C135.2, C136.2, C137.2, C138.2, C139.2, C140.1, C141.2, C142.2, D1.2 (A), D2.2 (A), D6.2 (A), D15.3 (A), D16.3 (A), H1.1, H2.1, H3.1, H4.1, J1.5, J1.6, J1.35, J1.36, J2.5, J2.6, J2.35, J2.36, J3.5, J3.6, J3.35, J3.36, J4.5, J4.6, J4.35, J4.36, J5.4, J6.4, J7.4, J8.4, J9.4, J10.4, J11.4, J12.4, J13.4, J14.4, J15.4, J16.4, J17.1, J17.3, J18.1, J18.3, J19.5, J19.7, J20.1, J20.3, J21.5, J21.7, R8.2, R21.1, R22.1, R23.1, R25.2, R27.2, R32.2, R33.1, R34.1, R37.2, R38.1, R39.1, R40.1, R41.1, R42.1, R45.2, R46.1, R47.1, R53.2, R55.2, R58.1, R59.1, R62.2, R64.2, R66.2, R69.1, R70.1, R73.2, R75.2, R77.2, R82.2, R83.1, R84.1, R87.2, R90.2, R91.1, R92.1, R95.2, R98.2, R99.2, R102.2, R105.2, R106.2, U1.3 (PG), U1.4 (PGTH), U1.8 (GND), U2.1 (SDO/SA0), U2.2 (SDX), U2.3 (SCX), U2.6 (GND), U2.7 (GND), U3.2 (RESERVED), U3.3 (GND), U3.9 (SDO/SA1), U3.12 (RESERVED), U4.2 (AGND), U4.4 (GND_BK), U4.12 (PGND), U4.15 (PGND), U4.18 (PGND), U4.26 (AGND), U4.41 (TPAD), U5.3 (GND), U6.3 (PG), U6.4 (PGTH), U6.8 (GND), U7.2 (RESERVED), U7.3 (GND), U7.9 (SDO/SA1), U7.12 (RESERVED), U8.3 (GND), U9.3 (PG), U9.4 (PGTH), U9.8 (GND), U10.3 (PG), U10.4 (PGTH), U10.8 (GND), U11.1 (SDO/SA0), U11.2 (SDX), U11.3 (SCX), U11.6 (GND), U11.7 (GND), U12.2 (AGND), U12.4 (GND_BK), U12.12 (PGND), U12.15 (PGND), U12.18 (PGND), U12.26 (AGND), U12.41 (TPAD), U13.3 (PG), U13.4 (PGTH), U13.8 (GND), U14.2 (AGND), U14.4 (GND_BK), U14.12 (PGND), U14.15 (PGND), U14.18 (PGND), U14.26 (AGND), U14.41 (TPAD), U15.3 (PG), U15.4 (PGTH), U15.8 (GND), U16.3 (GND), U17.2 (AGND), U17.4 (GND_BK), U17.12 (PGND), U17.15 (PGND), U17.18 (PGND), U17.26 (AGND), U17.41 (TPAD), U18.3 (PG), U18.4 (PGTH), U18.8 (GND), U19.3 (GND), U20.3 (PG), U20.4 (PGTH), U20.8 (GND), U21.3 (PG), U21.4 (PGTH), U21.8 (GND), U22.3 (GND), U23.3 (PG), U23.4 (PGTH), U23.8 (GND), U24.3 (GND), U25.12 (VSSA), U25.18 (VSS), U25.31 (VSS), U25.47 (VSS), U25.63 (VSS), U26.2 (GND), U27.3 (PG), U27.4 (PGTH), U27.8 (GND), U28.3 (GND), U29.12 (VSSA), U29.18 (VSS), U29.31 (VSS), U29.47 (VSS), U29.63 (VSS), U30.2 (GND), Y1.2, Y1.4, Y3.2, Y3.4
unnamed: JP23.2 (B), U26.1 (TXD)
unnamed: JP24.2 (B), U26.4 (RXD)
unnamed: JP26.2 (B), U30.1 (TXD)
unnamed: JP27.2 (B), U30.4 (RXD)
unnamed: C8.1, U3.4 (C1)
unnamed: C16.2, U4.8 (CP)
unnamed: C17.1, U4.7 (CPH)
unnamed: C17.2, U4.6 (CPL)
unnamed: C15.2, L1.1, U4.3 (FB_BK)
unnamed: L1.2, U4.5 (SW_BK)
unnamed: C27.1, U7.4 (C1)
unnamed: C46.2, U12.8 (CP)
unnamed: C47.1, U12.7 (CPH)
unnamed: C47.2, U12.6 (CPL)
unnamed: C45.2, L2.1, U12.3 (FB_BK)
unnamed: L2.2, U12.5 (SW_BK)
unnamed: C59.2, U14.8 (CP)
unnamed: C60.1, U14.7 (CPH)
unnamed: C60.2, U14.6 (CPL)
unnamed: C58.2, L3.1, U14.3 (FB_BK)
unnamed: L3.2, U14.5 (SW_BK)
unnamed: C75.2, U17.8 (CP)
unnamed: C76.1, U17.7 (CPH)
unnamed: C76.2, U17.6 (CPL)
unnamed: C74.2, L4.1, U17.3 (FB_BK)
unnamed: L4.2, U17.5 (SW_BK)
unnamed: C96.1, U24.4 (BST)
unnamed: R97.2, TP90.1, U24.5 (EN)
unnamed: C121.1, U28.4 (BST)
unnamed: R104.2, TP99.1, U28.5 (EN)

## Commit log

2026-01-22 Initial DTS + i2c Test
2026-01-22 spiTest + blinky
2026-01-22 Add README with setup instructions
    Added detailed setup instructions
2026-01-22 Rename project to UT-Core and revise README
    Updated project name and streamlined setup instructions.
2026-01-22 Revise README for UT CubeSat project details
    Updated project name and improved formatting in README.
2026-01-22 Format README commands for consistency
2026-01-23 Fix formatting in README for virtual environment activation
2026-01-23 Remove duplicate instructions for activating virtual environment
2026-01-23 CAN testing code added can to dts and made it a new app and got prj.conf sorted out for CAN main.c currently only fucntional for boot phase
2026-01-27 board dir change and opeoncd cfg change
2026-01-27 Setup DTS better for andLockTest app
2026-01-27 can overlay changes
2026-01-27 working CAN loopback with blinking LED
2026-01-28 Add core components for ADCS and CDH applications
    - Implement ReferenceGenerator class for attitude control with various mission modes.
    - Introduce Saturate utility functions for scalar and vector saturation.
    - Create Mission schedule configuration for orbital operations and events.
    - Develop main application logic for ADCS using Zephyr, including sensor data handling and control loop.
    - Set up CAN communication framework with message handling and command processing in CDH application.
    - Configure device tree overlay for FDCAN settings and PLL configuration.
2026-02-02 robust CAN b/w boards
2026-02-02 Implement CAN test applications with receiver and sender configurations
2026-02-04 robust can final changes to dts organization
2026-02-04 Refactor ADCS configuration and logging setup; update timing measurement function
2026-02-04 Add initial CAN test application files and configuration
2026-02-07 Refactor timing statistics structure and improve telemetry reading for I2C sensors; enhance logging configuration
2026-02-07 Add detailed documentation for I2C temperature telemetry functionality; enhance code comments and structure for clarity
2026-02-07 i2cTest: add comments to main.c
2026-02-09 Update comments in main.c for clarity on I2C temperature sensor functionality and input parameters
2026-02-17 spiFlashTest app first draft
2026-02-18 cdh main app changes
2026-02-20 mostly working SOH thread implementation
2026-03-23 Enhance blinky and spiFlashTest applications with new configurations and overlays. Added support for FRAM chips in spiFlashTest, including new source files for FRAM operations. Updated project config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
2026-03-23 Add initial implementation of spi_fram_tmr application with CMake and configuration files. Introduced main functionality for FRAM provisioning and scrubbing, along with GPIO overlays for LED control.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
2026-04-01 Add new spi_fram_tmr application with initial implementation for FRAM provisioning and scrubbing. Includes CMake and configuration files, GPIO overlays for LED control, and enhanced logging. Introduc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
2026-04-03 cdh main app completed and placeholders for other main apps made, about to restructure with more header files.
2026-04-15 Update blinky application configuration and main functionality. Changed UART logging backend to enabled, modified GPIO overlay for LED pin assignments, and replaced printf statements with printk for 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
2026-04-15 solar conglom progress
2026-04-21 UI interface + m5stamp support
2026-04-22 Add GNSS application with Orion B16 driver implementation
    Introduced a new GNSS application featuring the Orion B16 driver, including UART communication, navigation data parsing, and configuration commands. Added support for LED control in the overlay and e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
2026-04-22 works
2026-04-22 fully working currently testing 1 magnetorquer
2026-04-23 new parameters
2026-04-23 new params
2026-04-23 re did observer init
2026-04-24 re calibrated magnetometers
2026-04-24 Refactor CAN communication in BLDC application
    Updated the BLDC application to integrate CAN communication for motor RPM control. Introduced a new CAN command for setting wheel RPM references and modified the threading model to handle CAN message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
2026-04-24 calibrated rate gyros
2026-04-24 added mtq allocation
2026-04-24 better calibration for sensors and coordinate frames good now
2026-04-24 simplified adcsCore, added wheel and MTQ drivers, and readme for braydon
2026-04-25 sync airbearing demo
2026-04-25 COMPLETED solarconglom demo code and cdhMain with CAN b/w the two and fixed DTS for CAN to work on both boards
2026-04-25 Add CAN support and configuration for motorBoardCanTest application
    - Introduced CAN configuration in prj.conf for GPIO, CAN, and logging.
    - Added board overlay for FDCAN setup, mirroring the BLDC application.
    - Implemented main functionality in src/main.c, including CAN message handling and heartbeat transmission.
    - Adjusted motor control parameters and added telemetry logging for CAN communication.
    - Enhanced error handling for CAN device readiness and configuration.
2026-04-25 WIP EPS Demo code, refactored CDH with board config file and adjusted dts for CAN functionality on rev2 boards
2026-04-26 solar conglom finished and EPS finished
2026-04-26 Refactor CAN communication and telemetry logging in ground station UI
    - Updated CAN protocol to include a new command for setting wheel RPM.
    - Enhanced opcode naming in the CAN protocol for better clarity.
    - Modified CSV logger and UDP receiver to utilize the updated opcode naming.
    - Added telemetry logging for various subsystems including CDH, EPS, MOTOR, and SOLAR.
    - Improved thread handling and logging structure for better performance and readability.
2026-04-26 full GNSS with CAN
2026-04-26 Refactor ADCS application to integrate CAN communication
    - Updated ADCS application to support CAN messaging, including telemetry and command handling.
    - Added CAN device initialization and message queue management.
    - Introduced new opcodes for ADCS telemetry and commands in the CAN protocol.
    - Enhanced logging for CAN events and improved thread handling for message processing.
    - Modified board overlays to enable CAN functionality on the ut_core and adcsComputeTest boards.
2026-04-26 Implement wheel RPM command handling and magnetic dipole control in ADCS
    - Added functions to convert float RPM values to int16 and send wheel RPM commands for motors.
    - Integrated magnetic dipole command handling with PWM duty cycle adjustments based on ADCS outputs.
    - Updated CAN protocol to include new opcodes for setting wheel RPM and magnetic dipole commands.
    - Enhanced telemetry logging to reflect changes in motor control and dipole settings.
2026-04-26 feeds out RPMS
2026-04-26 getting simulation harness inside repo
2026-04-26 still working
2026-04-26 sim harness in repo
2026-04-26 working
2026-04-26 good sim
2026-04-26 Implement EPS load command handling and update CAN protocol
    - Added command handling for EPS load control, allowing enabling/disabling of individual or all loads.
    - Introduced new opcode for EPS load commands in the CAN protocol.
    - Updated logging to reflect EPS load command processing and outcomes.
    - Adjusted file paths for header inclusions to improve portability across environments.
2026-04-26 CDH and GNSS and EPS CAN handling
2026-04-26 made bang bang for MTQ's
2026-04-26 bang bang complete
2026-04-26 new area sum
2026-04-26 boolean flags now
2026-04-26 mtq's perfect
2026-04-26 testing motors
2026-04-27 demo ready
2026-04-27 demo ready actually
2026-04-27 Enhance CDH functionality with temperature telemetry and configuration updates
    - Enabled temperature telemetry for up to six I2C temperature sensors, including data structure and mutex for thread safety.
    - Updated CAN protocol to include a new opcode for CDH temperature telemetry.
    - Modified main configuration to support flash and SPI functionalities.
    - Adjusted motor enable settings to allow simultaneous operation of all motors.
    - Introduced a new source file for threaded flight architecture in the CDH application.
2026-05-04 added UID read code test app
